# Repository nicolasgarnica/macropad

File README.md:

# macropad
 3x3 macropad schematics

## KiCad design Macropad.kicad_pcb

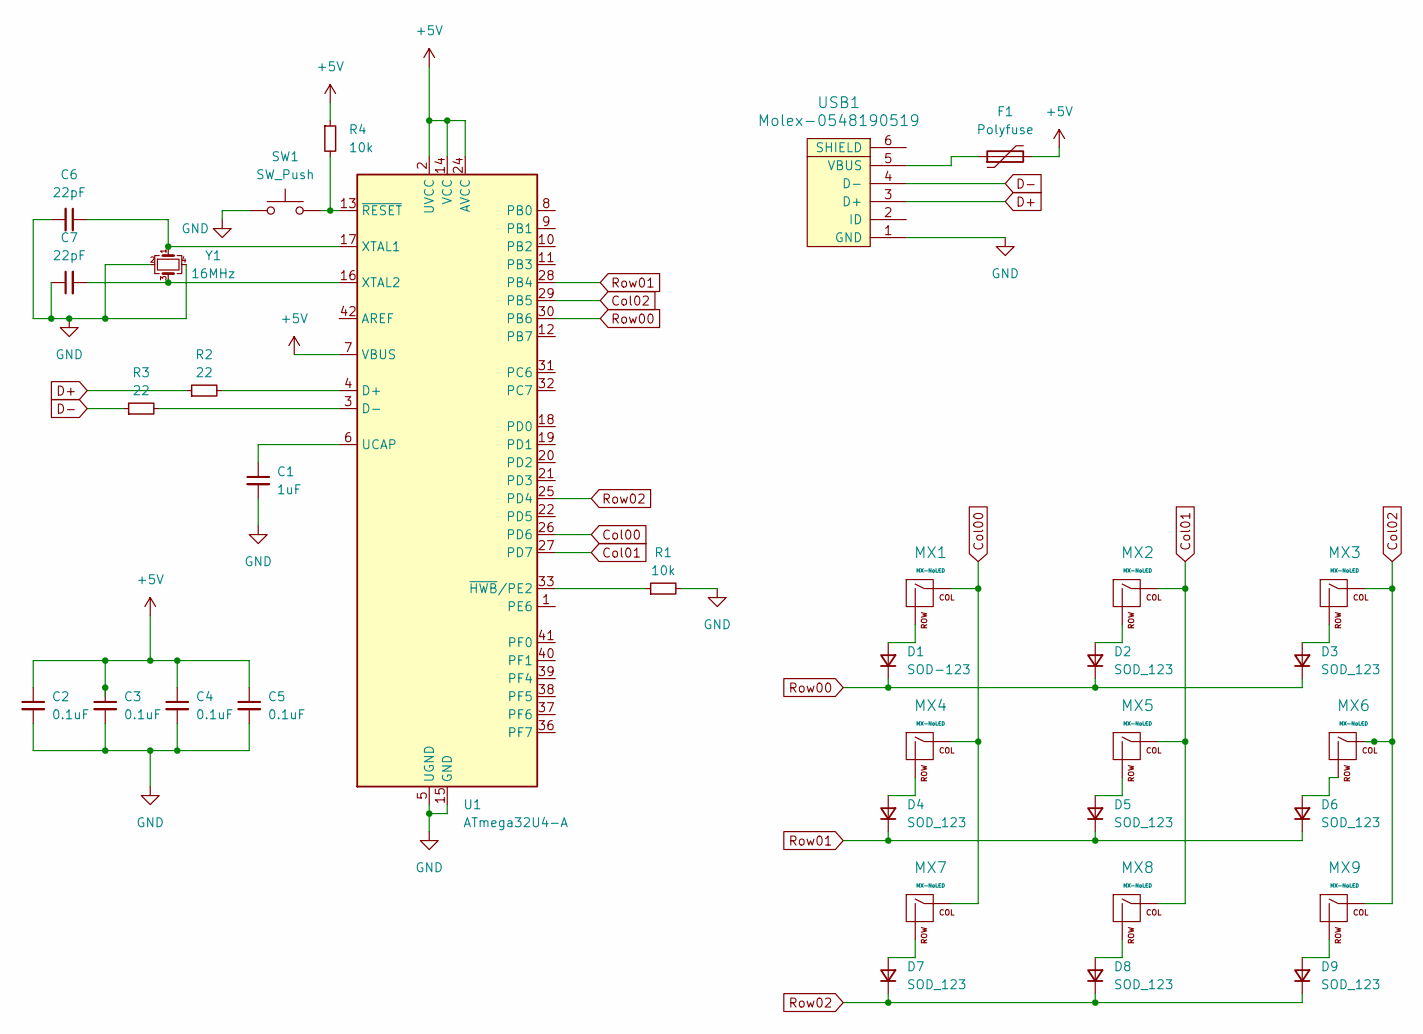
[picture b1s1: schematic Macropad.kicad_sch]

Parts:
C1: 1uF; C_0805_2012Metric
C2, C3, C4, C5: 0.1uF; C_0805_2012Metric
C6, C7: 22pF; C_0805_2012Metric
D1: SOD-123; D_SOD-123
D2, D3, D4, D5, D6, D7, D8, D9: SOD_123; D_SOD-123
F1: Polyfuse; Fuse_1206_3216Metric
MX1, MX2, MX3, MX4, MX5, MX6, MX7, MX8, MX9: MX-NoLED; MX-1U-NoLED
R1, R4: 10k; R_0805_2012Metric
R2, R3: 22; R_0805_2012Metric
SW1: SW_Push; SKQG-1155865
U1: ATmega32U4-A; TQFP-44_10x10mm_P0.8mm
USB1: Molex-0548190519; Molex-0548190589
Y1: 16MHz; Crystal_SMD_3225-4Pin_3.2x2.5mm

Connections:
+5V: C2.1, C3.1, C4.1, C5.1, F1.2, R4.1, U1.2 (UVCC), U1.7 (VBUS), U1.14 (VCC), U1.24 (AVCC), U1.34 (VCC), U1.44 (AVCC)
Col00: MX1.1 (COL), MX4.1 (COL), MX7.1 (COL), U1.26 (PD6)
Col01: MX2.1 (COL), MX5.1 (COL), MX8.1 (COL), U1.27 (PD7)
Col02: MX3.1 (COL), MX6.1 (COL), MX9.1 (COL), U1.29 (PB5)
D+: R2.1, USB1.3 (D+)
D-: R3.1, USB1.4 (D-)
GND: C1.2, C2.2, C3.2, C4.2, C5.2, C6.2, C7.1, R1.2, SW1.1, U1.5 (UGND), U1.15 (GND), U1.23 (GND), U1.35 (GND), U1.43 (GND), USB1.1 (GND), Y1.2, Y1.4
unnamed: D1.2 (A), MX1.2 (ROW)
unnamed: D2.2 (A), MX2.2 (ROW)
unnamed: D3.2 (A), MX3.2 (ROW)
unnamed: D4.2 (A), MX4.2 (ROW)
unnamed: D5.2 (A), MX5.2 (ROW)
unnamed: D6.2 (A), MX6.2 (ROW)
unnamed: D7.2 (A), MX7.2 (ROW)
unnamed: D8.2 (A), MX8.2 (ROW)
unnamed: D9.2 (A), MX9.2 (ROW)
unnamed: R2.2, U1.4 (D+)
unnamed: R3.2, U1.3 (D-)
unnamed: C1.1, U1.6 (UCAP)
unnamed: C6.1, U1.17 (XTAL1), Y1.1
unnamed: C7.2, U1.16 (XTAL2), Y1.3
unnamed: R1.1, U1.33 (~HWB/PE2)
unnamed: R4.2, SW1.2, U1.13 (~RESET)
unnamed: F1.1, USB1.5 (VBUS)
Row00: D1.1 (K), D2.1 (K), D3.1 (K), U1.30 (PB6)
Row01: D4.1 (K), D5.1 (K), D6.1 (K), U1.28 (PB4)
Row02: D7.1 (K), D8.1 (K), D9.1 (K), U1.25 (PD4)

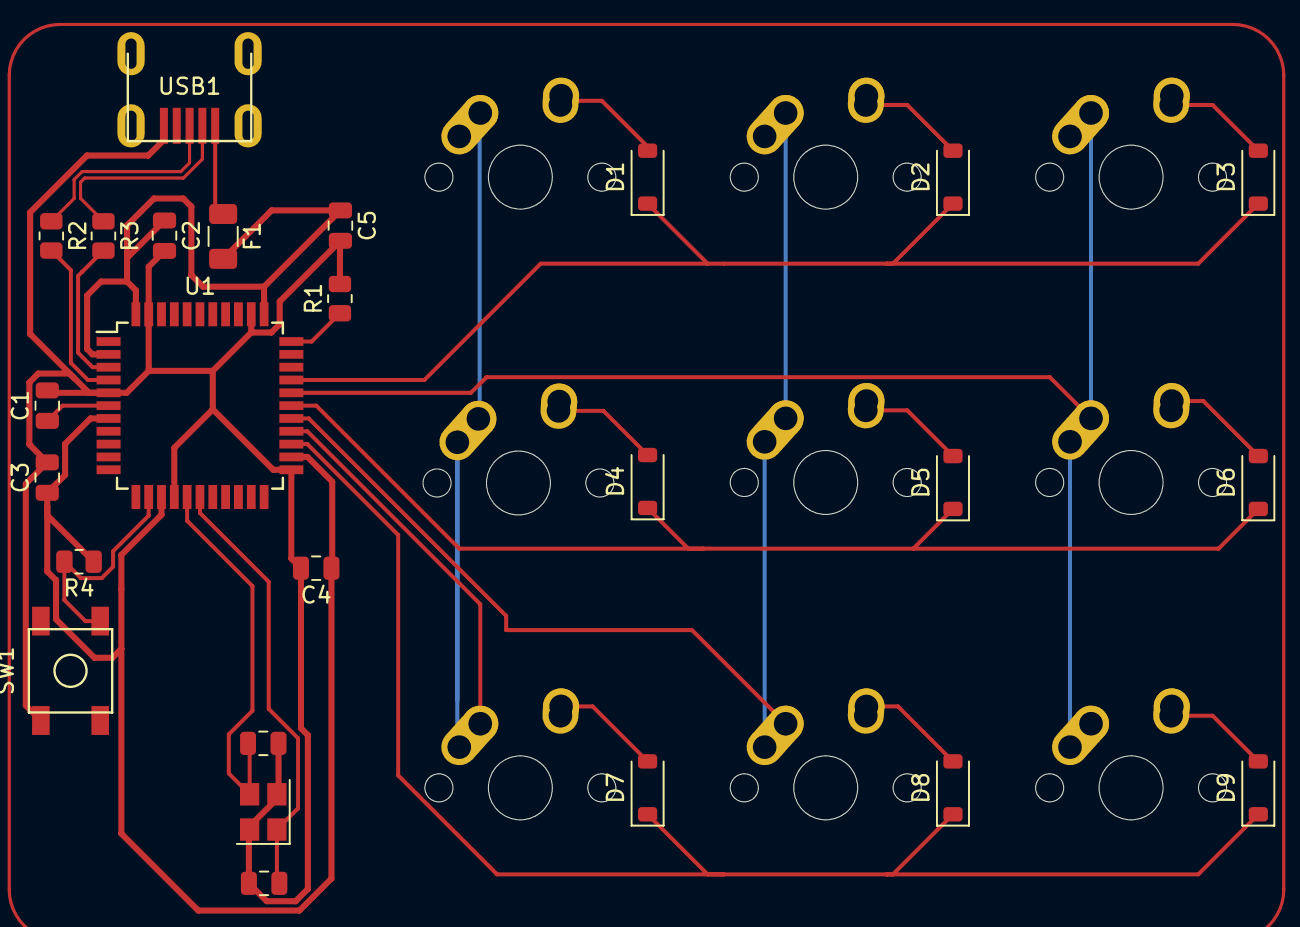
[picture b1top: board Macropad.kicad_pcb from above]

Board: 2 copper layers, 34 parts (0 on the bottom side), 27 nets.

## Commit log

2023-07-24 Schematics for a 3x3 macropad
    This is a small project to get back into PCB design and schematic capture.
2023-07-24 Add submodules for keyboards
2023-07-24 adding libraries
    Adding keyboard specific libraries to the project
2023-07-24 Schematic capture
    Schematic for the 3x3 macropad has been finished (did not add the rows and columns to the MCU).
2023-07-30 routing of the components
    pcb layout done
2023-07-30 Gerber files
